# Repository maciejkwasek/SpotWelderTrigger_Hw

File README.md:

# SpotWelderTrigger_Hw

## What it is
SpotWelderTrigger_Hw is a project of PCB designed for **[SpotWelderController](https://github.com/maciejkwasek/SpotWelderController)** firmware.
The project is a two layer printed circuit board with THT elements, made in KiCad 5.1.7.
You can generate gerber files and order PCB in your local manufacturer by your own.

## Images

## Pinout
Soon.

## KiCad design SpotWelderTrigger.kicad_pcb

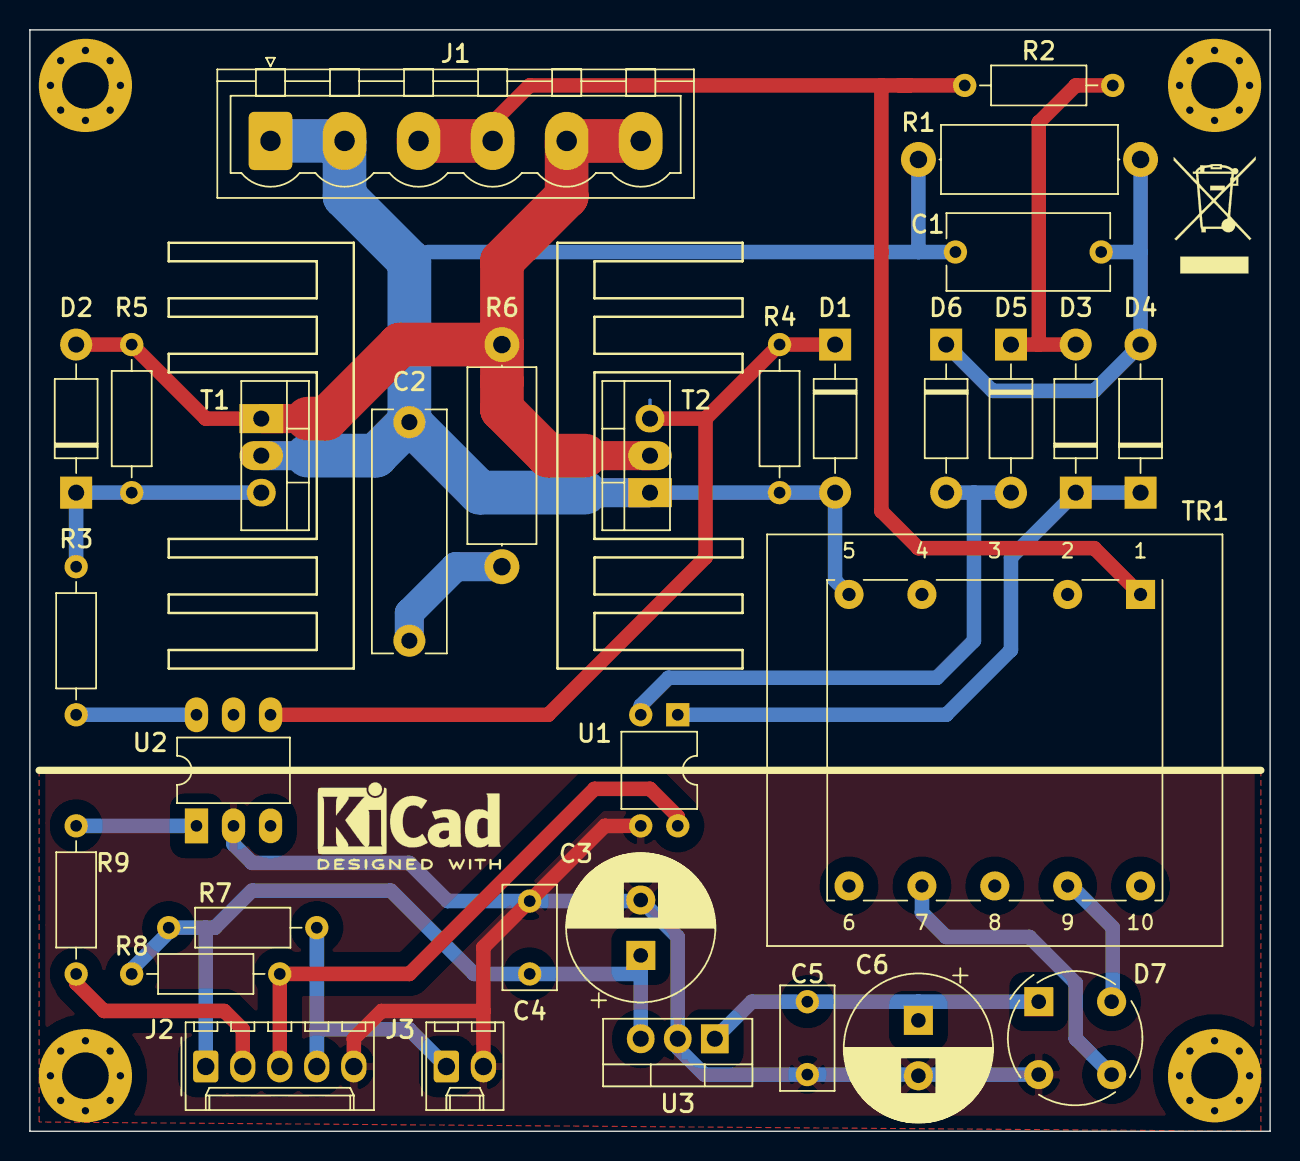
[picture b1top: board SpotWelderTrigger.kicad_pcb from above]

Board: 2 copper layers, 85.1 x 75.6 mm, 31 parts (0 on the bottom side), 20 nets.

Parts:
C1: 47nF/400V; C_Rect_L11.0mm_W5.1mm_P10.00mm_MKT
C2: 100nF/400V; C_Rect_L16.5mm_W4.9mm_P15.00mm_MKT
C3: 100uF; CP_Radial_D10.0mm_P3.80mm
C4, C5: 100nF; C_Rect_L7.0mm_W3.5mm_P5.00mm
C6: 470uF; CP_Radial_D10.0mm_P3.80mm
D1, D2, D3, D4, D5, D6: 1N4007; D_DO-41_SOD81_P10.16mm_Horizontal
D7: D_Bridge_+-AA; Diode_Bridge_Round_D9.0mm
J1: Conn_01x06_Male; PhoenixContact_MSTBVA_2,5_6-G-5,08_1x06_P5.08mm_Vertical
J2: Conn_01x05_Male; Molex_KK-254_AE-6410-05A_1x05_P2.54mm_Vertical
J3: Conn_01x02_Male; Molex_KK-254_AE-6410-02A_1x02_P2.54mm_Vertical
R1: 1M; R_Axial_DIN0414_L11.9mm_D4.5mm_P15.24mm_Horizontal
R2, R4, R5: 330; R_Axial_DIN0207_L6.3mm_D2.5mm_P10.16mm_Horizontal
R3: 390; R_Axial_DIN0207_L6.3mm_D2.5mm_P10.16mm_Horizontal
R6: 2k2/2W; R_Axial_DIN0414_L11.9mm_D4.5mm_P15.24mm_Horizontal
R7, R8: 4k7; R_Axial_DIN0207_L6.3mm_D2.5mm_P10.16mm_Horizontal
R9: 220; R_Axial_DIN0207_L6.3mm_D2.5mm_P10.16mm_Horizontal
T1, T2: TYN616; TO-220-3_Vertical
TR1: TEZ2.0/D; Transformer_Breve_TEZ-28x33
U1: EL817; DIP-4_W7.62mm
U2: MOC3021M; DIP-6_W7.62mm_LongPads
U3: LM7805_TO220; TO-220-3_Vertical

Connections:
GND: C3.2, C4.2, C5.2, C6.2, D7.2, J2.5, J3.2, U1.3, U2.2, U3.2
unnamed: C1.1, C2.2, D1.2, J1.1, J1.2, R1.1, R4.1, T1.2, T2.1, TR1.5
unnamed: C1.2, D4.2, D6.1, R1.2
unnamed: C2.1, R6.1
unnamed: C5.1, C6.1, D7.1, U3.1
unnamed: D1.1, R4.2, T2.3, U2.4
unnamed: D2.1, R3.1, R5.1, T1.3
unnamed: D2.2, J1.5, J1.6, R5.2, R6.2, T1.1, T2.2
unnamed: D3.1, D4.1, U1.1
unnamed: D3.2, D5.1, R2.2
unnamed: D5.2, D6.2, U1.2
unnamed: D7.3, TR1.7
unnamed: D7.4, TR1.9
unnamed: J1.3, J1.4, R2.1, TR1.1
unnamed: J2.2, R9.2
unnamed: J2.3, R8.2, U1.4
unnamed: J2.4, J3.1, R7.2
unnamed: R3.2, U2.6
unnamed: R9.1, U2.1
VCC: C3.1, C4.1, J2.1, R7.1, R8.1, U3.3

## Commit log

2020-10-18 Initial version of schematic
2020-10-20 SSFH620 replaced to EL817, page settings added
2021-01-04 Add logic power supply
2021-01-10 Add footprints for most components
2021-04-16 Add very first pcb layout, refactor
2021-08-27 Full layout
2021-08-27 J1,J2 merged to one connector
2021-11-15 Add polygons
2021-11-15 Select gerber ploting options
2021-11-18 Add fp-info-cache to gitignore
2021-12-03 Add LICENSE file
2021-12-03 Add README.md
2021-12-11 Add sample images
2021-12-11 Resize images
